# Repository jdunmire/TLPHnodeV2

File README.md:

TLPHnodeV2
==========
This is a [KiCad](http://kicad-pcb.org/) project for an ESP8266 based
temperature, light, pressure, and humidity node.

Additional information about this node can be found at the 
[Sensor Nodes](http://sensornodeinfo.rockingdlabs.com) website.

Copyright Jerry Dunmire 2017.

This documentation describes Open Hardware and is licensed under the
CERN OHL v. 1.2.

You may redistribute and modify this documentation under the terms of
the CERN OHL v.1.2. (LICENSE.txt). This documentation is distributed
WITHOUT ANY EXPRESS OR IMPLIED WARRANTY, INCLUDING OF MERCHANTABILITY,
SATISFACTORY QUALITY AND FITNESS FOR A PARTICULAR PURPOSE. Please see
the CERN OHL v.1.2 for applicable conditions

Guidelines on how to apply the CERN OHL v1.2 are in the
cern_ohl_v_1_2_howto.pdf file.

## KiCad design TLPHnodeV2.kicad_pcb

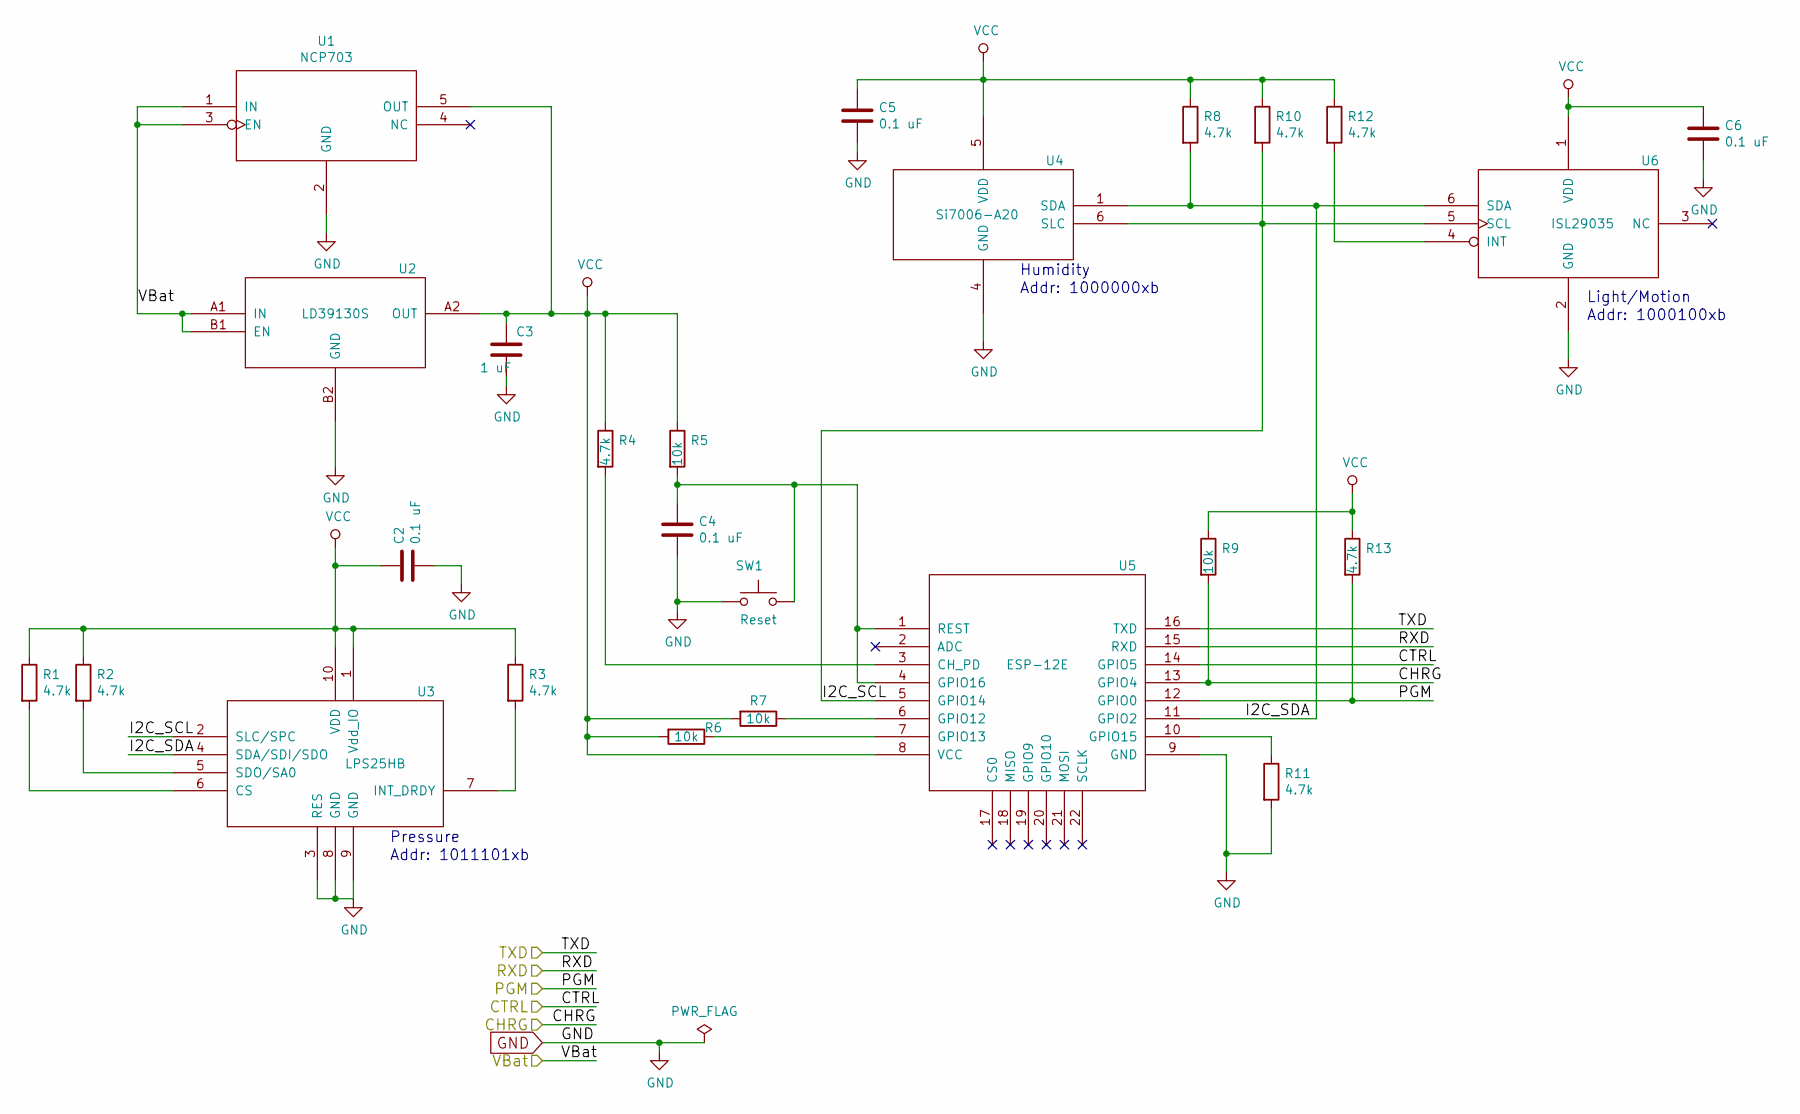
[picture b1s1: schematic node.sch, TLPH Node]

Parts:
C2, C4, C5, C6: 0.1 uF; C_0603
C3: 1 uF; C_0603
R1, R2, R3, R4, R8, R10, R11, R12, R13: 4.7k; R_0603
R5, R6, R7, R9: 10k; R_0603
SW1: Reset; ESwitch-SMD-4
U1: NCP703; NCP703-TSOP-5
U2: LD39130S; LD39130S-FlipChip-4
U3: LPS25HB; LPS25HB-HLGA-10L-2.5x2.5mm
U4: Si7006-A20; Si7006_A20-DFN-6
U5: ESP-12E
U6: ISL29035; ISL29035-DFN-6-1.5x1.6mm_Pitch0.5mm

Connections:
+BATT: U1.1 (IN), U1.3 (EN), U2.A1 (IN), U2.B1 (EN); also elsewhere on the board
/node/CHRG: R9.2, U5.13 (GPIO4); also elsewhere on the board
/node/CTRL: U5.14 (GPIO5); also elsewhere on the board
/node/I2C_SCL: R10.2, U3.2 (SLC/SPC), U4.6 (SLC), U5.5 (GPIO14), U6.5 (SCL)
/node/I2C_SDA: R8.2, U3.4 (SDA/SDI/SDO), U4.1 (SDA), U5.11 (GPIO2), U6.6 (SDA)
/node/PGM: R13.2, U5.12 (GPIO0); also elsewhere on the board
/node/RXD: U5.15 (RXD); also elsewhere on the board
/node/TXD: U5.16 (TXD); also elsewhere on the board
GND: C2.2, C3.2, C4.2, C5.2, C6.2, R11.2, SW1.1, U1.2 (GND), U2.B2 (GND), U3.3 (RES), U3.8 (GND), U3.9 (GND), U4.4 (GND), U5.9 (GND), U6.2 (GND); also elsewhere on the board
unnamed: C4.1, R5.2, SW1.2, U5.1 (REST), U5.4 (GPIO16)
unnamed: R1.2, U3.6 (CS)
unnamed: R2.2, U3.5 (SDO/SA0)
unnamed: R3.2, U3.7 (INT_DRDY)
unnamed: R4.2, U5.3 (CH_PD)
unnamed: R6.1, U5.7 (GPIO13)
unnamed: R7.1, U5.6 (GPIO12)
unnamed: R11.1, U5.10 (GPIO15)
unnamed: R12.2, U6.4 (INT)
VCC: C2.1, C3.1, C5.1, C6.1, R1.1, R2.1, R3.1, R4.1, R5.1, R6.2, R7.2, R8.1, R9.1, R10.1, R12.1, R13.1, U1.5 (OUT), U2.A2 (OUT), U3.1 (Vdd_IO), U3.10 (VDD), U4.5 (VDD), U5.8 (VCC), U6.1 (VDD)

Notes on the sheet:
Pressure
Light/Motion
Humidity
Addr: 1011101xb
Addr: 1000000xb
Addr: 1000100xb

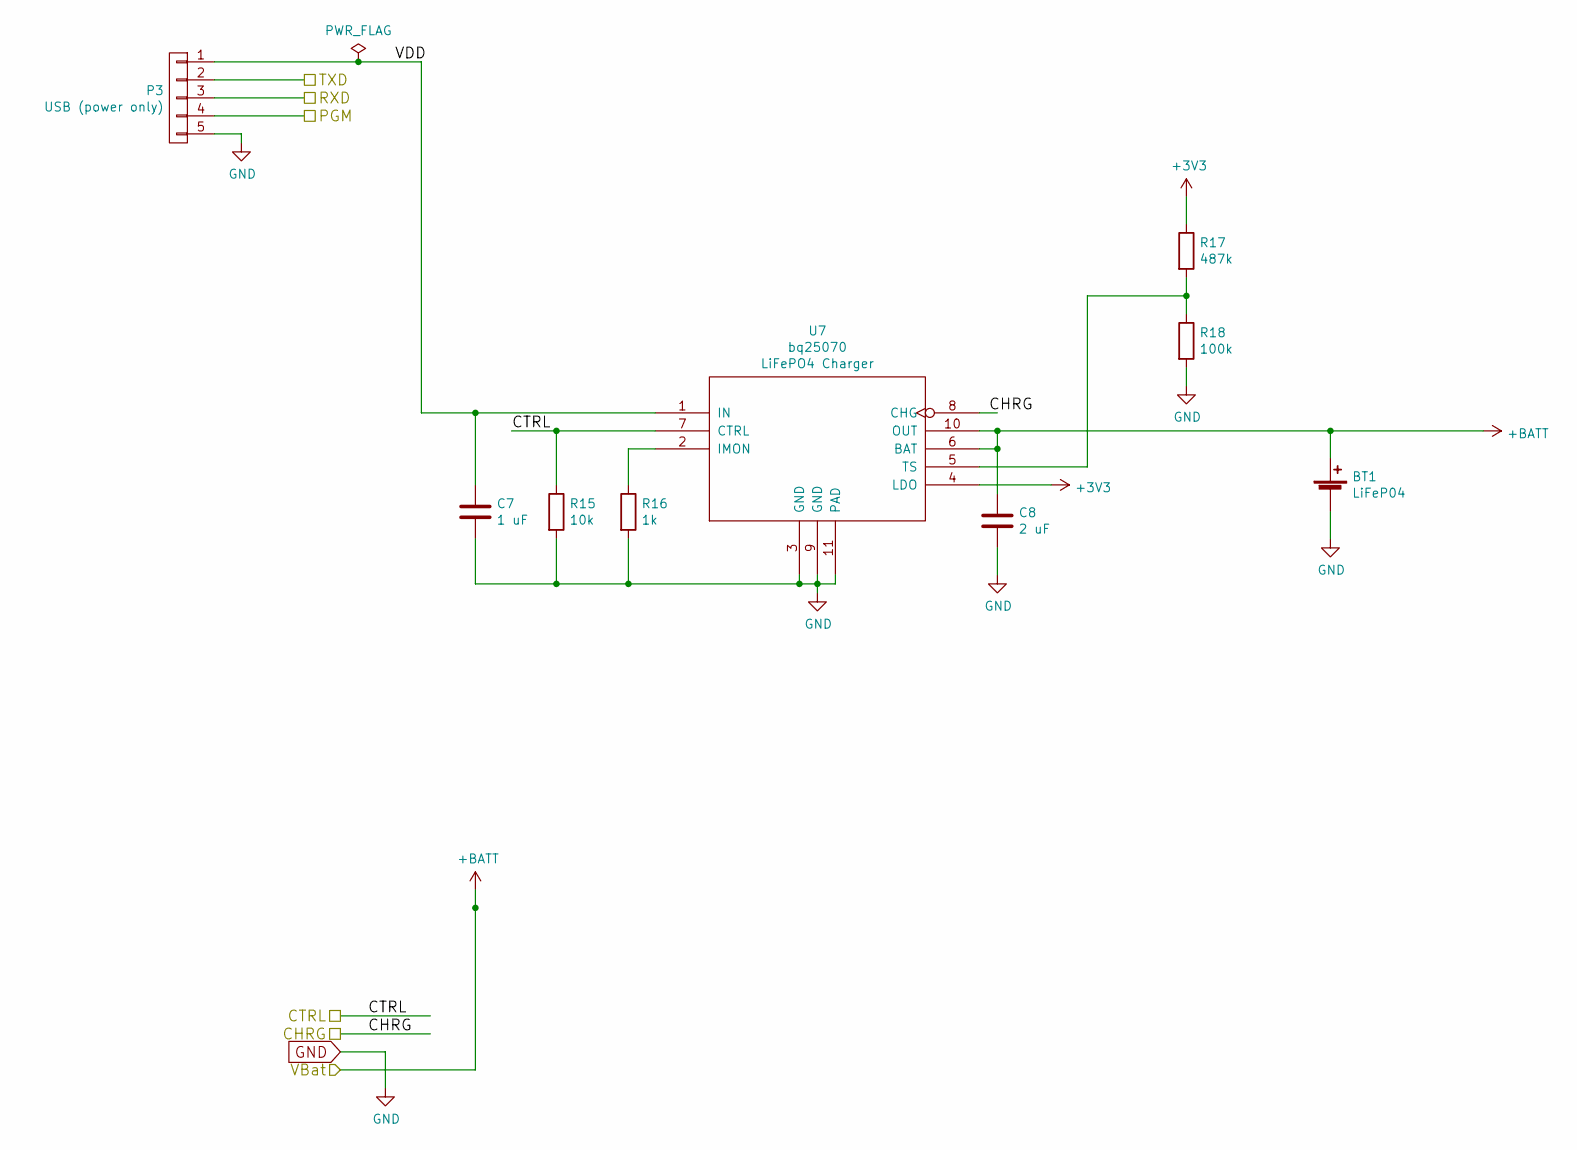
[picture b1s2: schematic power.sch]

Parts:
BT1: LiFeP04; JST_PH_B2B-PH-SM4-TB_02x2.00mm_Straight
C7: 1 uF; C_0603
C8: 2 uF; C_0603
P3: USB (power only); USB_Micro-B_10103594-0001LF
R15: 10k; R_0603
R16: 1k; R_0603
R17: 487k; R_0603
R18: 100k; R_0603
U7: bq25070; bq25070_DQC_10-DQC10_P84X2P4

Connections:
+3V3: R17.1, U7.4 (LDO)
+BATT: BT1.1 (+), C8.1, U7.6 (BAT), U7.10 (OUT); also elsewhere on the board
/node/CHRG: U7.8 (CHG); also elsewhere on the board
/node/CTRL: R15.1, U7.7 (CTRL); also elsewhere on the board
/node/PGM: P3.4; also elsewhere on the board
/node/RXD: P3.3; also elsewhere on the board
/node/TXD: P3.2; also elsewhere on the board
/power/VDD: C7.1, P3.1, U7.1 (IN)
GND: BT1.2 (-), C7.2, C8.2, P3.5, R15.2, R16.2, R18.2, U7.3 (GND), U7.9 (GND), U7.11 (PAD); also elsewhere on the board
unnamed: R16.1, U7.2 (IMON)
unnamed: R17.2, R18.1, U7.5 (TS)

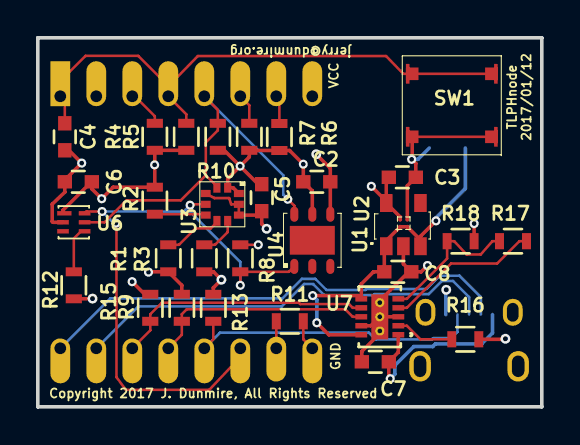
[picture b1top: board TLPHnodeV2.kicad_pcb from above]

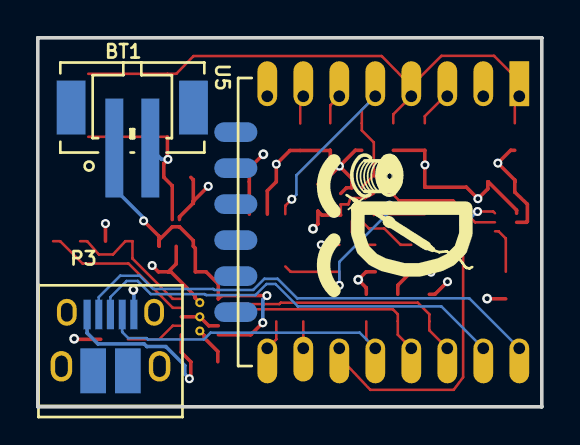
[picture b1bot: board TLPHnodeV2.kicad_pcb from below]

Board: 4 copper layers, 28.0 x 20.5 mm, 35 parts (4 on the bottom side), 23 nets.

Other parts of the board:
Ref**: RockingDLogo_9x7

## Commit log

2016-12-31 Combine TLPHnode and nodePwr
    - Create a single board based on the two original
    - Battery connector (BT1) has been changed from rt-angle to vert.
    On branch master
2016-12-31 Add project level file
    On branch master
    modified: TLPHnodeV2.pro
2016-12-31 Get ready for new routing
    - remove old parts and all traces
    - import new netlist
    On branch master
    modified: TLPHnodeV2.kicad_pcb
2016-12-31 Remove extra resistor on CTRL
    On branch master
    modified: TLPHnodeV2.net
    modified: node.sch
2016-12-31 Remove C1
    - C8 should be adequate for both the regulators (U1, U2) and the
    charger (U7)
2016-12-31 CP- initial placement
    On branch master
    modified: TLPHnodeV2.kicad_pcb
    modified: TLPHnodeV2.pro
2016-12-31 CP - refined placement
    - Rotated battery connector
2016-12-31 CP - routing started
    - Need two swap CTRL and CHRG to make routing cleaner
2016-12-31 Swap ESP-8266 signals for charger control
    - Swap CHRG and CTRL to make layout cleaner
    On branch master
    modified: TLPHnodeV2.kicad_pcb
    modified: TLPHnodeV2.net
    modified: node.sch
2016-12-31 CP - signals routed
    On branch master
    modified: TLPHnodeV2.kicad_pcb
2017-01-07 Relocate USB connector to side
2017-01-08 CP - before swapping CHRG and CTRL
2017-01-08 CP - Swapped CTRL and CHRG
    On branch usbSide
    modified: TLPHnodeV2.net
    modified: node.sch
2017-01-08 CP - move R9 to follow CRTL and CHRG
    On branch usbSide
    modified: TLPHnodeV2.net
    modified: node.sch
2017-01-08 CP - routed and passed DRC
    On branch usbSide
    modified: TLPHnodeV2.kicad_pcb
2017-01-11 Update copyright date
2017-01-13 Move traces and add logo
    - move a few traces so that they won't be exposed through the solder
    mask
    - Add a logo
    - Set the date
    On branch master
    modified: TLPHnodeV2.kicad_pcb
2017-01-13 Save version used to generate gerber files
    On branch master
    modified: TLPHnodeV2.kicad_pcb
2017-01-13 Change board name to TLPHnodeV2
    On branch master
    modified: TLPHnodeV2.kicad_pcb
2017-02-03 Fix NCP703 symbol
    Pin 3 EN was marked as an inverted clock. It is actually a logic signal
    that should be pulled up to enable.

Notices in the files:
TLPHnodeV2.kicad_pcb:
Copyright 2017 J. Dunmire, All Rights Reserved
